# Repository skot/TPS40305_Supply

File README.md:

# TPS40305 Supply
Texas Instruments TPS40305 based power supply.

Low voltage, high current buck controller.

- Input: DC 4V - 5.5V
- Output: adjustable between 1.38V and 1.66V using pot
- Output Current: 25A (at 1.5V)
- Seems to work!

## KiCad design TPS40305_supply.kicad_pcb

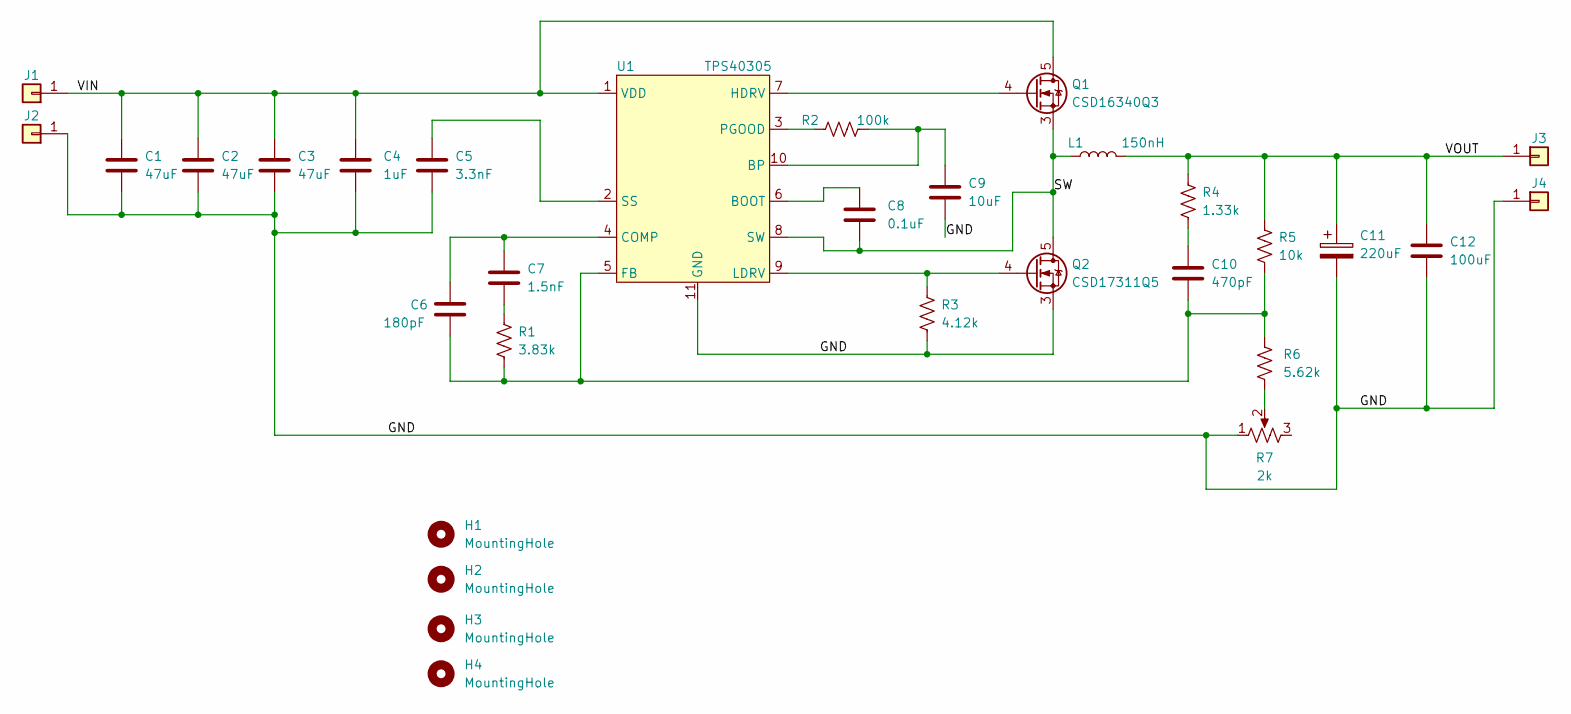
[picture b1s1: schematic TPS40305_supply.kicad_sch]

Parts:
C1, C2, C3: 47uF; C_1210_3225Metric; PARTNO GRM32ER61C476KE15L
C4: 1uF; C_0805_2012Metric
C5: 3.3nF; C_0402_1005Metric
C6: 180pF; C_0805_2012Metric
C7: 1.5nF; C_0805_2012Metric
C8: 0.1uF; C_0402_1005Metric
C9: 10uF; C_0805_2012Metric
C10: 470pF; C_0805_2012Metric
C11: 220uF; CAP_2R5TPE220MAFB; PARTNO 2R5TPE220MAFB
C12: 100uF; C_1206_3216Metric; PARTNO C3216X5R0J107M160AB
H1, H2, H3, H4: MountingHole; MountingHole_2.2mm_M2
J1, J2, J3, J4: Conn_01x01; 63862-1; PARTNO 63862-1
L1: 150nH; FP1005R1-R15-R; PARTNO FP1005R1-R15-R
Q1: CSD16340Q3; PARTNO CSD16340Q3
Q2: CSD17311Q5; PARTNO CSD17311Q5
R1: 3.83k; R_0402_1005Metric
R2: 100k; R_0402_1005Metric
R3: 4.12k; R_0402_1005Metric
R4: 1.33k; R_0402_1005Metric
R5: 10k; R_0402_1005Metric
R6: 5.62k; R_0402_1005Metric
R7: 2k; ST4ETB202; PARTNO ST4ETB202
U1: TPS40305; PARTNO TPS40305DRCT

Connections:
/GND: C1.2, C2.2, C3.2, C4.2, C5.2, C9.2, C11.2, C12.2, J2.1, J4.1, Q2.1, Q2.2, Q2.3 (S), R3.2, R7.1, U1.11 (GND)
/SW: C8.2, L1.1, Q1.1, Q1.2, Q1.3 (S), Q2.5 (D), U1.8 (SW)
/VIN: C1.1, C2.1, C3.1, C4.1, J1.1, Q1.5 (D), U1.1 (VDD)
/VOUT: C11.1, C12.1, J3.1, L1.2, R4.1, R5.1
unnamed: C5.1, U1.2 (SS)
unnamed: C6.1, C7.1, U1.4 (COMP)
unnamed: C7.2, R1.1
unnamed: C8.1, U1.6 (BOOT)
unnamed: C9.1, R2.2, U1.10 (BP)
unnamed: C10.1, R4.2
unnamed: C6.2, C10.2, R1.2, R5.2, R6.1, U1.5 (FB)
unnamed: Q1.4 (G), U1.7 (HDRV)
unnamed: Q2.4 (G), R3.1, U1.9 (LDRV)
unnamed: R2.1, U1.3 (PGOOD)
unnamed: R6.2, R7.2

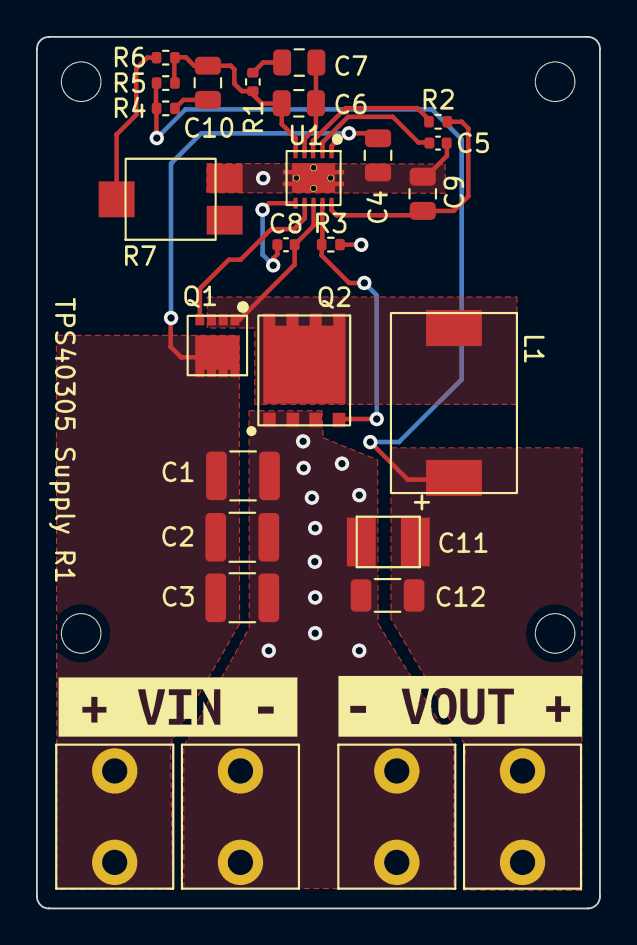
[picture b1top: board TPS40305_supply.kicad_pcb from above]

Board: 2 copper layers, 31.3 x 48.4 mm, 33 parts (0 on the bottom side), 15 nets.

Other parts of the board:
kibuzzard-633B51DB: G***; kibuzzard-633B51DB
kibuzzard-633B5210: G***; kibuzzard-633B5210

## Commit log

2022-09-13 initial import
2022-09-13 added the jellybean footprints
2022-09-13 started on some of the mosfet footprints
2022-09-30 added footprints
2022-09-30 added spade connectors ("we need a spade if we're gonna dig a pit.")
2022-09-30 fixed problem with mosfet pad
2022-10-03 more layout
2022-10-03 initial layout and routing complete
2022-10-03 added silkscreen and 3D part CAD files
2022-10-03 added preview jpg
2022-10-04 added DK part numbers and generated BOM
2022-10-04 added gerbers
2022-10-04 updated busted DK PN
2022-10-04 updated preview pic with mounting holes
2022-10-25 readme update after building R1 boards
